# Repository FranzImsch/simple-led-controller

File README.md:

# Simplest LED Controller

# Abstract
As home automation becomes more and more popular, more and more smart home enabled devices replace old-fashioned switch-controlled devices. However, different systems have several advantages and disadvantages that makes it hard to choose the perfect system. A solution to that is to make your own smart home devices.  
This project’s goal was to minimise both the complexity and the cost of such a self-built device. 

# Features
The “Simplest-LED-Controller” features 3 usable PWM-controlled channels (and one on-off channel) and is being programmed using the Arduino framework. It consists of very basic components with the exception of the nRF52-module. The latter is the MCU of the project and it communicates via ESB-protocol with a gateway. This module consumes very little energy while idling, making it a much better solution than WiFi-based ones.

# Hardware
The LEDs are controlled using 4 Mosfets (IRLZ44N) that are broadly available. The power for the MCU is supplied by a LM2596-Module that can be purchased very cheaply. For basic functionality, only the nRF-module, the buck converter, the Mosfets, the screw terminals and a few 0603 10k resistors are necessary.  
```Note: always adjust the step down converter's voltage to 3.3V before assembling!```  
The board also features an interface for a FTDI (or equivalent) and a breakout of the I2C pins, so a sensor could be connected to the MCU in addition.  
The board is being programmed through a Tag-Connect interface using a J-Link or similar.

# Software
As for the software, the MySensors library is used to allow an easy implementation of the ESB-protocol of the nRF52.

## Partlist

|Component           |Value                    | Package |
|--------------------|-------------------------|---------|
|C6                  | 10µF Cap                |0603     |
|C7                  | 0.1µF Cap               |0603     |
|D2, D3              | LED                     |0603     |
|IC3                 | E73_2G4M04S             |         |
|J1                  | Socket Header 6P        |         |
|J2                  | Socket Header 4P        |         |
|J4                  | Screw Terminal (3*3P)   |         |
|Q1-Q4               | IRLZ44N                 ||TO-220  |
|R1-R4, R6           | 10K Resistor            |0603     |
|R5, R17             | 1K Resistor             |0603     |
|R7, R8              | I2C Pullups             |0603     |
|U$1                 | LM2596-MODULE           |         |

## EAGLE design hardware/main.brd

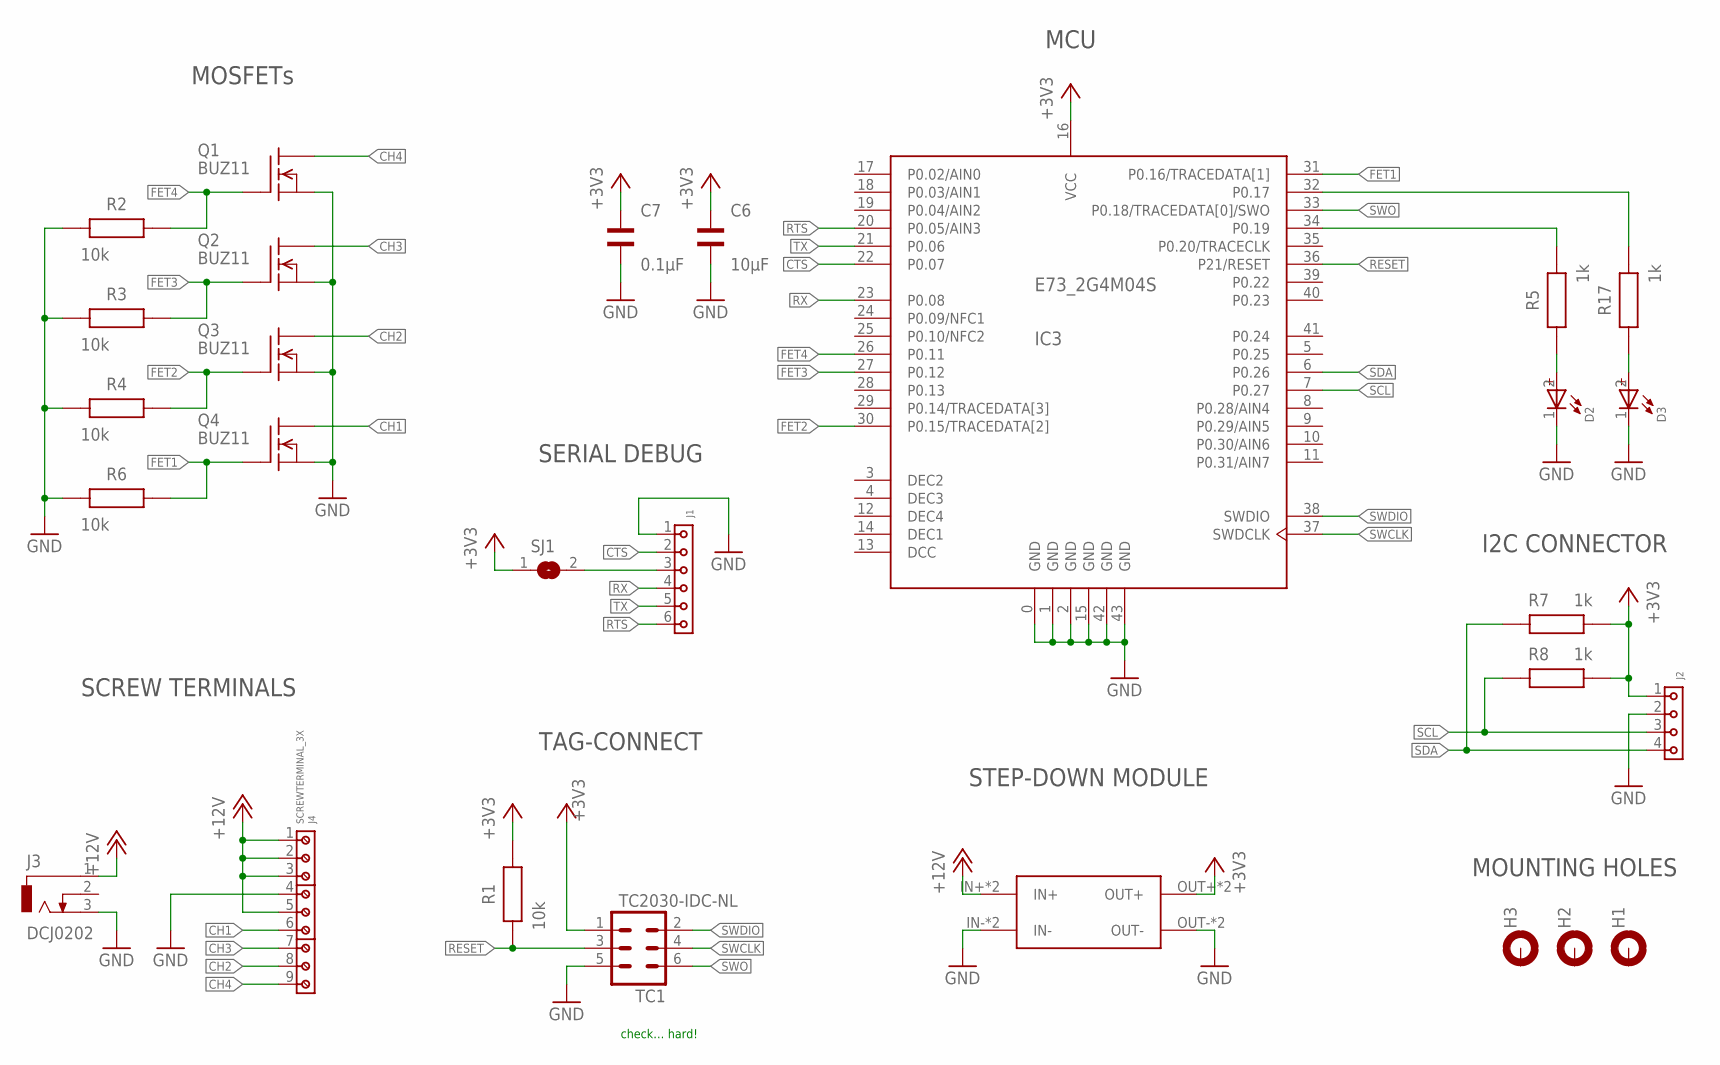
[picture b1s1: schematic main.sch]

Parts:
C6: 10µF; WCAP-CSGP_0603_REFLOW
C7: 0.1µF; WCAP-CSGP_0603_REFLOW
D2, D3: WL-SMCW_0603_150060BS75000; WL-SMCW_0603
H1, H2, H3: MOUNT-PAD-ROUND3.2; 3,2-PAD
IC3: E73_2G4M04S
J1: 6130XX11821_61300611821; 61300611821
J2: 6130XX11821_61300411821; 61300411821
J3: DCJ0202
J4: SCREWTERMINAL_3X; 691102710003
Q1, Q2, Q3, Q4: BUZ11; TO220
R1, R2, R3, R4, R6: 10k; WRIS-PSMB_0603_1.6X0.8X0.35X0.6(LXWXHXPW)
R5, R7, R8, R17: 1k; WRIS-PSMB_0603_1.6X0.8X0.35X0.6(LXWXHXPW)
SJ1: SJ
TC1: TC2030-IDC-NL
U$1: LM2596-MODULE

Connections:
+3V3: C6.2, C7.2, IC3.16 (VCC), J2.1, R1.2, R7.1, R8.1, SJ1.1, TC1.1, U$1.OUT+, U$1.OUT+1 (OUT+)
+12V: J3.1, J4.1, J4.2, J4.3, J4.5, U$1.IN+, U$1.IN+1 (IN+)
CH1: J4.6, Q4.2 (D)
CH2: J4.8, Q3.2 (D)
CH3: J4.7, Q2.2 (D)
CH4: J4.9, Q1.2 (D)
CTS: IC3.22 (P0.07), J1.2
DCC: IC3.13 (DCC)
DEC1: IC3.14 (DEC1)
DEC2: IC3.3 (DEC2)
DEC3: IC3.4 (DEC3)
DEC4: IC3.12 (DEC4)
FET1: IC3.31 (P0.16/TRACEDATA[1]), Q4.1 (G), R6.2
FET2: IC3.30 (P0.15/TRACEDATA[2]), Q3.1 (G), R4.2
FET3: IC3.27 (P0.12), Q2.1 (G), R3.2
FET4: IC3.26 (P0.11), Q1.1 (G), R2.2
GND: C6.1, C7.1, D2.1 (-), D3.1 (-), IC3.0 (GND), IC3.1 (GND), IC3.2 (GND), IC3.15 (GND), IC3.42 (GND), IC3.43 (GND), J1.1, J2.2, J3.3, J4.4, Q1.3 (S), Q2.3 (S), Q3.3 (S), Q4.3 (S), R2.1, R3.1, R4.1, R6.1, TC1.5, U$1.IN-, U$1.IN-1 (IN-), U$1.OUT-, U$1.OUT-1 (OUT-)
unnamed: J1.3, SJ1.2
unnamed: D2.2 (+), R5.2
unnamed: D3.2 (+), R17.2
unnamed: IC3.32 (P0.17), R17.1
unnamed: IC3.34 (P0.19), R5.1
RESET: IC3.36 (P21/RESET), R1.1, TC1.3
RTS: IC3.20 (P0.05/AIN3), J1.6
RX: IC3.23 (P0.08), J1.4
SCL: IC3.7 (P0.27), J2.3, R8.2
SDA: IC3.6 (P0.26), J2.4, R7.2
SWCLK: IC3.37 (SWDCLK), TC1.4
SWDIO: IC3.38 (SWDIO), TC1.2
SWO: IC3.33 (P0.18/TRACEDATA[0]/SWO), TC1.6
TX: IC3.21 (P0.06), J1.5

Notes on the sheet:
check… hard!
MCU
MOSFETs
SCREW TERMINALS
STEP-DOWN MODULE
TAG-CONNECT
MOUNTING HOLES
SERIAL DEBUG
I2C CONNECTOR

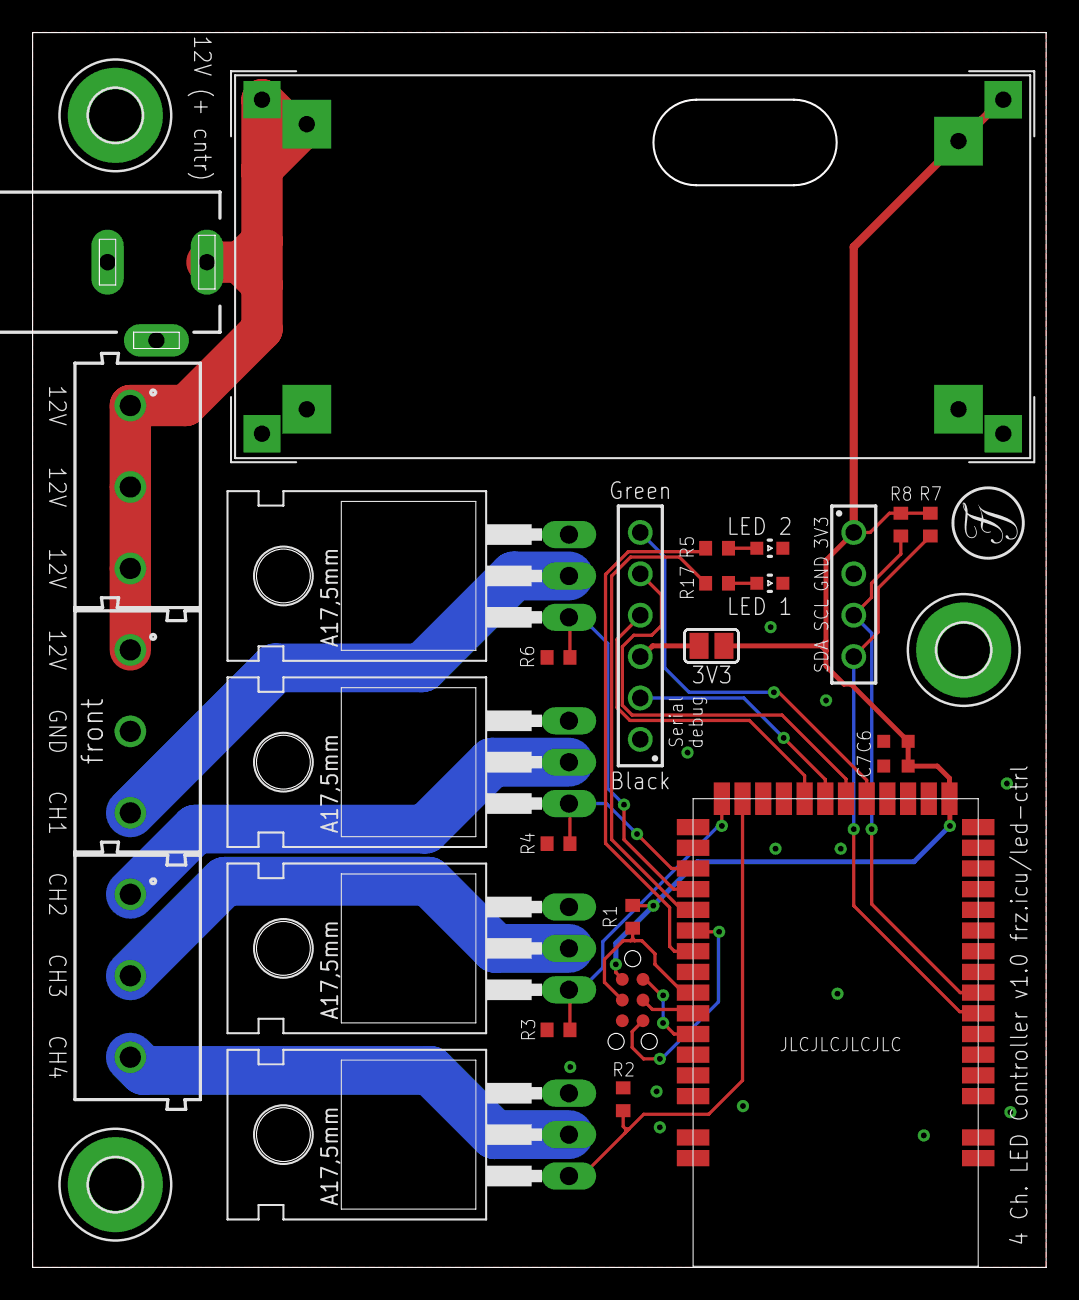
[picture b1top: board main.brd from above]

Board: 2 copper layers, 62.1 x 75.7 mm, 28 parts (0 on the bottom side), 26 nets.

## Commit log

2020-10-17 initialising repo
2020-10-17 v1.0
2020-10-19 added dc barrel jack
2020-10-19 added barrel jack
2020-10-19 hardware files
2020-11-09 enhanced Readme after testing

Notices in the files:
parts and their libraries:
580060716001_Eagle_WRIS-PSMB_rev19a: Copyright: Würth Elektronik
